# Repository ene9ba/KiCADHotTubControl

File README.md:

# KiCADHotTubControl

PCB HotTubControl
Used as Client over MQTT to OpenHab
Controller Wemos 1 mini (ESP 8266)
Two relay channels to control the massage pump and filter pump
One input to check Waterlevel
Four channels for DS1820 temperatur sensor

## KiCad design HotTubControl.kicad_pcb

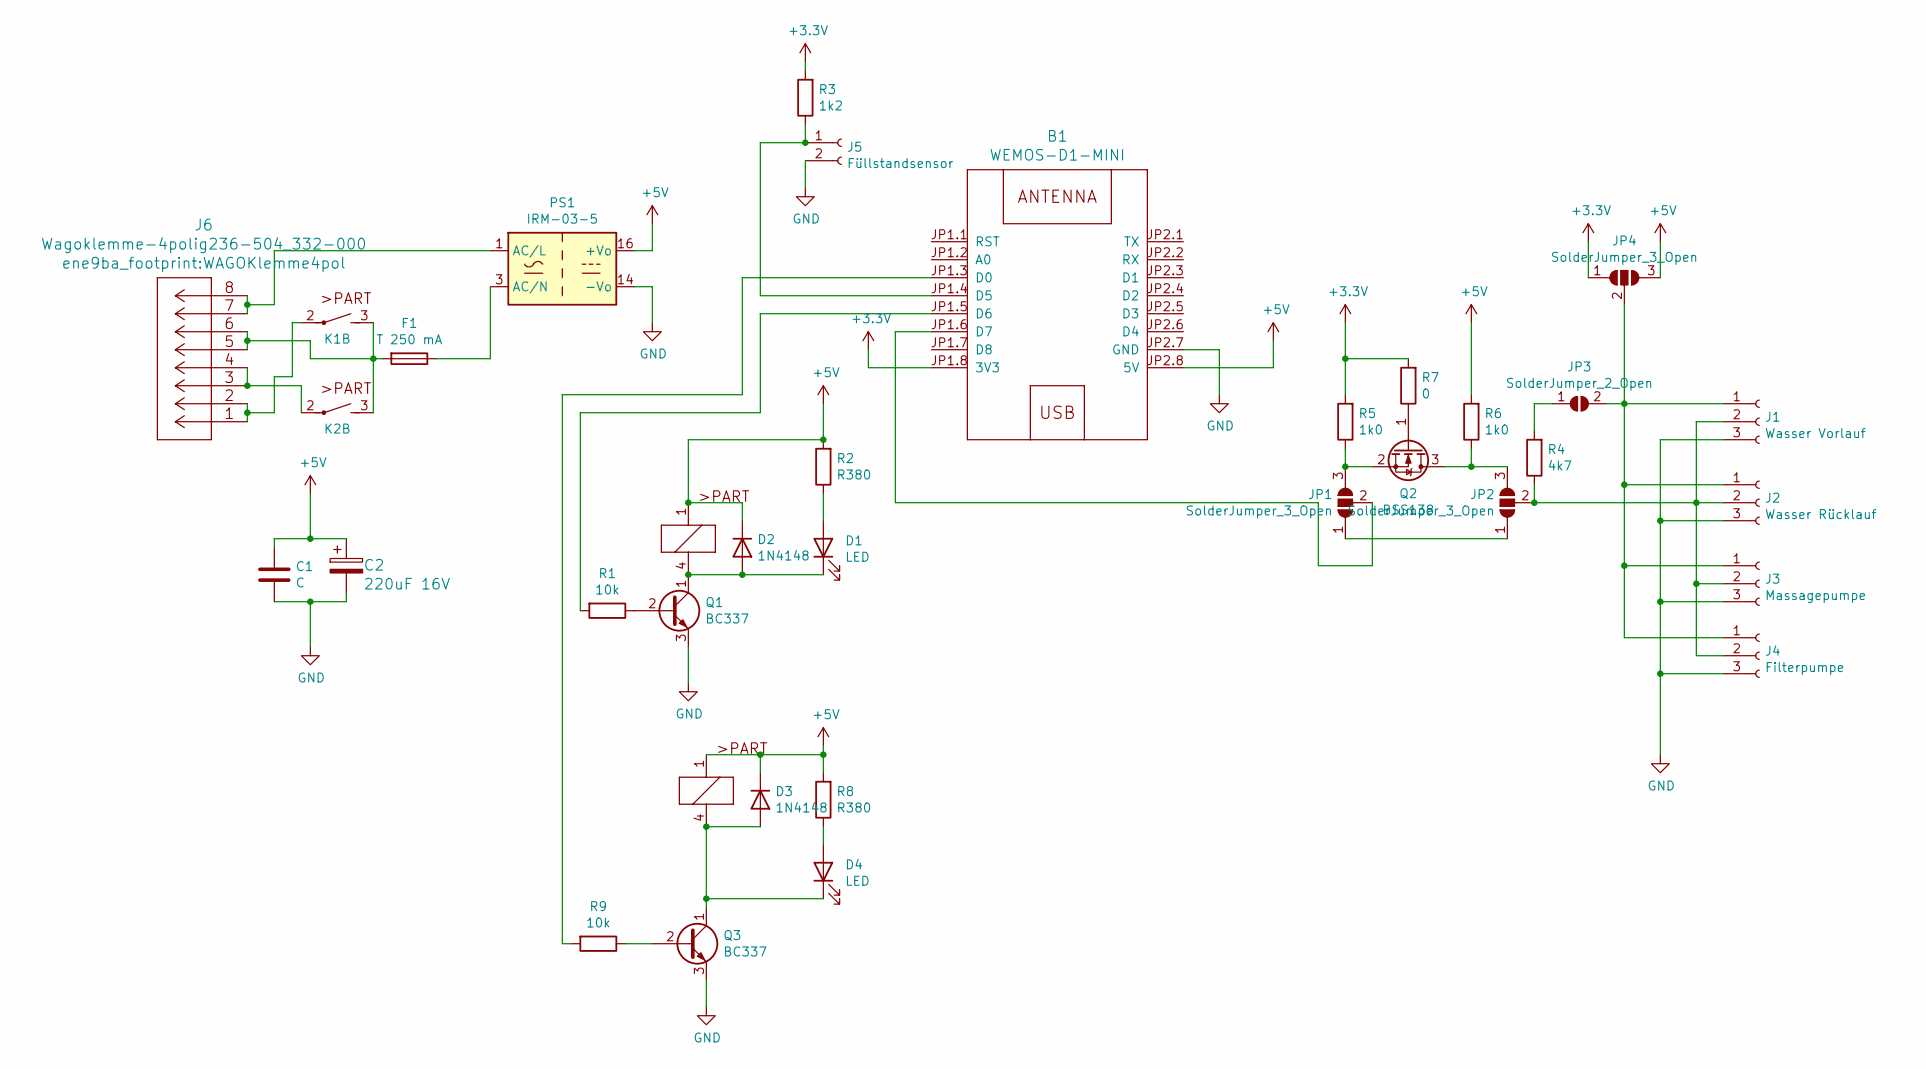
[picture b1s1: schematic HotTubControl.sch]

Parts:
B1: WEMOS-D1-MINI
C1: C; C050-025X075
C2: 220uF 16V; C_Radial_D10.0mm_H20.0mm_P5.00mm
D1, D4: LED; LED_D5.0mm
D2, D3: 1N4148; D_DO-35_SOD27_P7.62mm_Horizontal
F1: T 250 mA; Fuseholder_TR5_Littelfuse_No560_No460
J1: Wasser Vorlauf; PinSocket_1x03_P2.54mm_Vertical
J2: Wasser Rücklauf; PinSocket_1x03_P2.54mm_Vertical
J3: Massagepumpe; PinSocket_1x03_P2.54mm_Vertical
J4: Filterpumpe; PinSocket_1x03_P2.54mm_Vertical
J5: Füllstandsensor; PinSocket_1x02_P2.54mm_Vertical
J6: Wagoklemme-4polig236-504_332-000; WAGOKlemme4pol
JP1, JP2, JP4: SolderJumper_3_Open; SolderJumper-3_P1.3mm_Open_Pad1.0x1.5mm
JP3: SolderJumper_2_Open; SolderJumper-2_P1.3mm_Open_Pad1.0x1.5mm
K1, K2: JV-KT; JV24SKT
PS1: IRM-03-5; Converter_ACDC_MeanWell_IRM-03-xx_THT
Q1, Q3: BC337; TO-92_Inline
Q2: BSS138; SOT-23
R1, R9: 10k; R_Axial_DIN0207_L6.3mm_D2.5mm_P15.24mm_Horizontal
R2, R8: R380; R_Axial_DIN0207_L6.3mm_D2.5mm_P15.24mm_Horizontal
R3: 1k2; R_Axial_DIN0207_L6.3mm_D2.5mm_P15.24mm_Horizontal
R4: 4k7; R_Axial_DIN0207_L6.3mm_D2.5mm_P15.24mm_Horizontal
R5, R6: 1k0; R_Axial_DIN0207_L6.3mm_D2.5mm_P15.24mm_Horizontal
R7: 0; R_Axial_DIN0207_L6.3mm_D2.5mm_P15.24mm_Horizontal

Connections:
+3V3: B1.JP1.8 (3V3), JP4.1 (A), R3.2, R5.2, R7.2
+5V: B1.JP2.8 (5V), C1.1, C2.1, D2.1 (K), D3.1 (K), JP4.3 (B), K1.1, K2.1, PS1.16 (+Vo), R2.2, R6.2, R8.2
GND: B1.JP2.7 (GND), C1.2, C2.2, J1.3, J2.3, J3.3, J4.3, J5.2, PS1.14 (-Vo), Q1.3 (E), Q3.3 (E)
unnamed: B1.JP1.3 (D0), R9.2
unnamed: B1.JP1.4 (D5), J5.1, R3.1
unnamed: B1.JP1.5 (D6), R1.2
unnamed: B1.JP1.6 (D7), JP1.2 (C)
unnamed: D1.1 (K), D2.2 (A), K1.4 (2), Q1.1 (C)
unnamed: D1.2 (A), R2.1
unnamed: D3.2 (A), D4.1 (K), K2.4 (2), Q3.1 (C)
unnamed: D4.2 (A), R8.1
unnamed: F1.1, PS1.3 (AC/N)
unnamed: F1.2, J6.5, J6.6, K1.3 (S), K2.3 (S)
unnamed: J1.1, J2.1, J3.1, J4.1, JP3.2 (B), JP4.2 (C)
unnamed: J1.2, J2.2, J3.2, J4.2, JP2.2 (C), R4.1
unnamed: J6.1, J6.2, K1.2
unnamed: J6.3, J6.4, K2.2
unnamed: J6.7, J6.8, PS1.1 (AC/L)
unnamed: JP1.1 (A), JP2.1 (A)
unnamed: JP1.3 (B), Q2.2 (S), R5.1
unnamed: JP2.3 (B), Q2.3 (D), R6.1
unnamed: JP3.1 (A), R4.2
unnamed: Q1.2 (B), R1.1
unnamed: Q2.1 (G), R7.1
unnamed: Q3.2 (B), R9.1

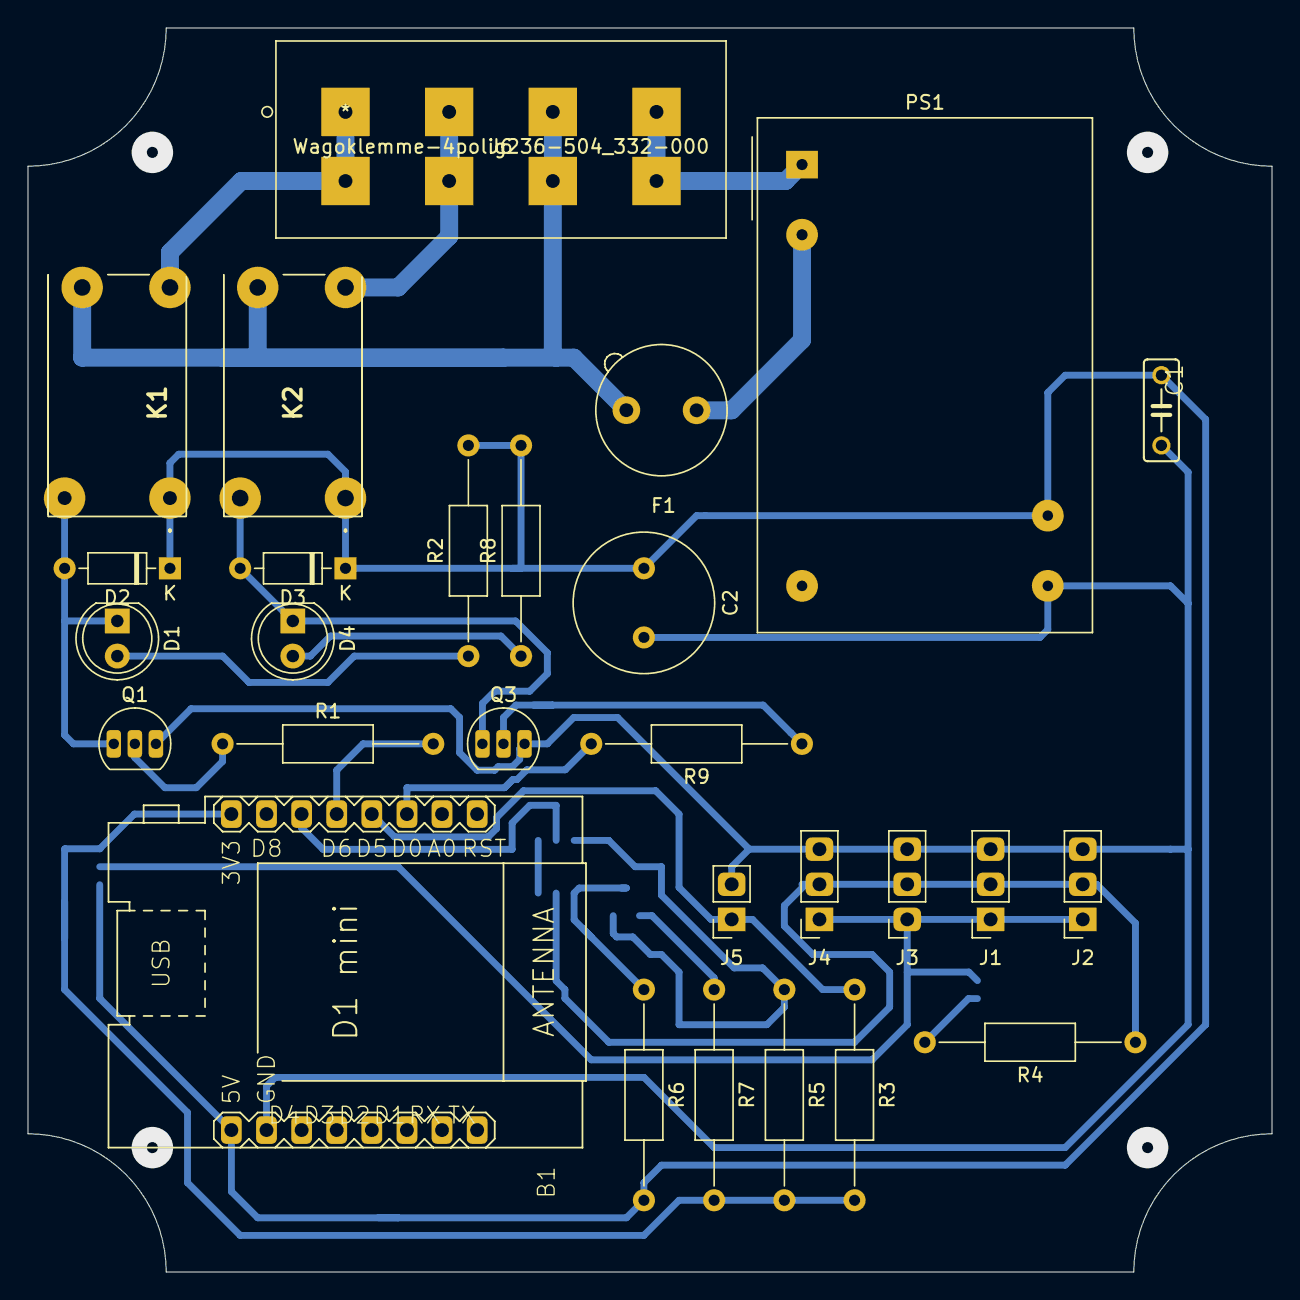
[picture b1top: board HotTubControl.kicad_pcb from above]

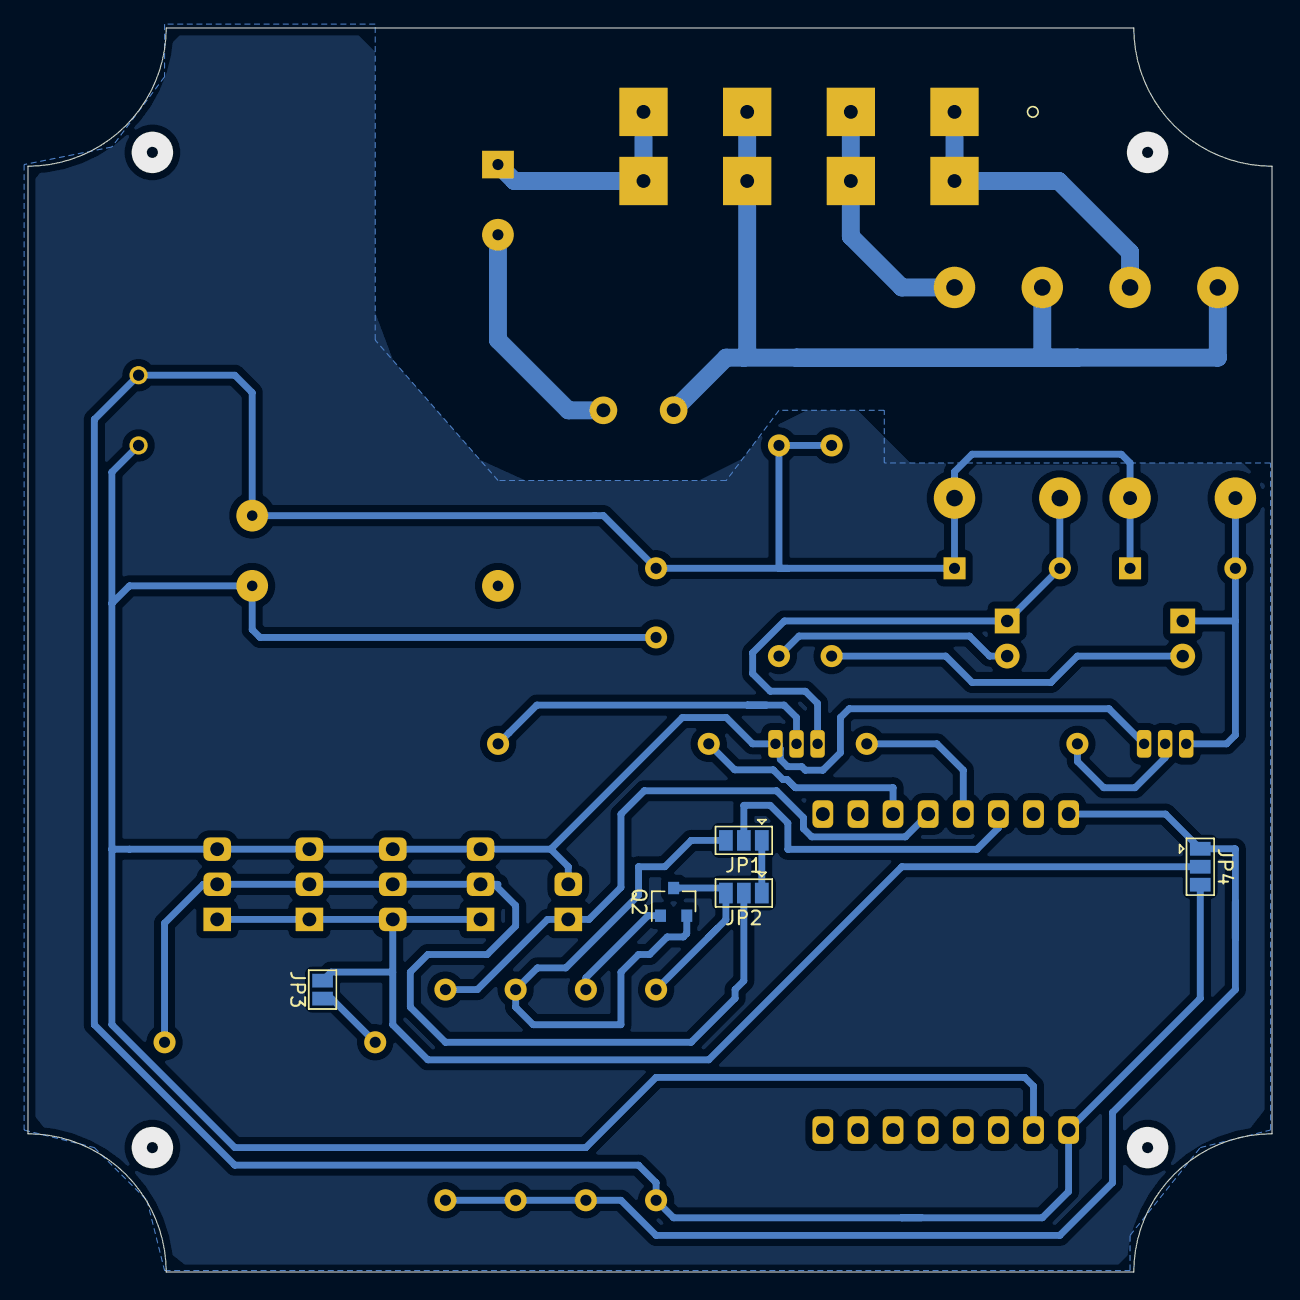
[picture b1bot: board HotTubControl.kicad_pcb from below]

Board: 2 copper layers, 90.0 x 90.0 mm, 33 parts (5 on the bottom side), 25 nets.

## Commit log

2021-10-14 neue 3d Elemente
2021-11-12 V2.0 added one channesl
    Ein zweiter Relaiskanal zu Steuerung der Massagepumpe wurde integriert
2021-12-01 Version 2
    added second Relay
2021-12-01 Anpassung Ausfüllungen
2021-12-01 with ibom
2021-12-02 inc bom

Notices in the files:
parts and their libraries:
Copyright 2021 Accelerated Designs. All rights reserved.
